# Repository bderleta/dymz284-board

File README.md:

# dymz284-board
Dual YMZ284 synth board design using retro technology (THT elements, DIP packages). Board designed to fit Hammond 1455C802 enclosure.

An application of ATMega8 8-bit MCU in PDIP package capable of driving two of YMZ284 PSG chips. This is a simplified derivative of [DYM2149](https://github.com/bderleta/dym2149-board) and runs similar firmware, but there are some differences:

- PSG data inputs are driven from '595 shift register controlled via SPI, instead of `PORTA` (note: '595 used has to be capable of running at 8 MHz+, as firmware uses SPI2X, making SPI clock equal to Tosc/2; plain SN74HC595 won't make it)
- Control pin assignments and names are different
- There is no JTAG and no SPI RAM
- Instead of single INT2 button, there are two hardware-debounced interrupt triggering buttons (INT0 and INT1)

As YMZ284 has only single DAC output, there is no mixing stage present, first PSG is assigned to the left channel, second - to the right. In contrary to YM2149 chips, YMZ has clock divider permamently enabled, therefore it is necessary to provide generator twice as fast to achieve identical behavior. This device has been tested with 4 MHz and 3.579545 MHz CXOs.

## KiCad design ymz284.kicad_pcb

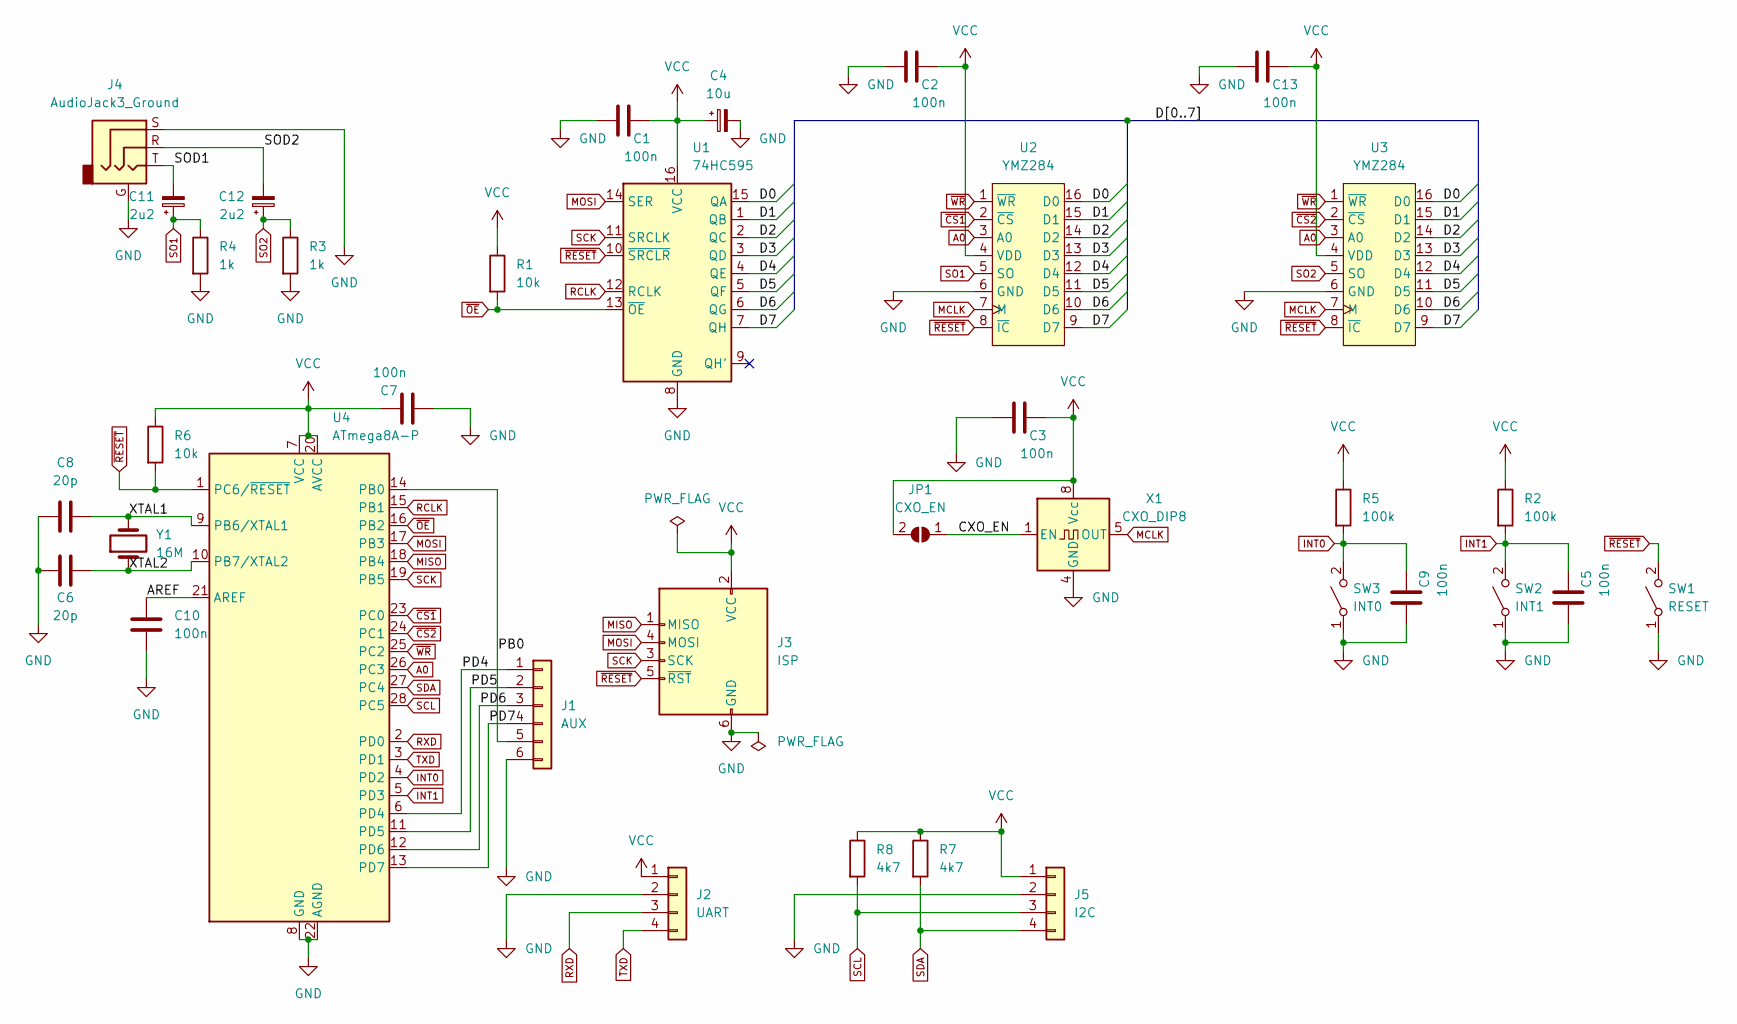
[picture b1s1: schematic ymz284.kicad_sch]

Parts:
C1, C2, C3, C5, C7, C9, C10, C13: 100n; C_Disc_D5.0mm_W2.5mm_P5.00mm
C4: 10u; CP_Radial_D5.0mm_P2.50mm
C6, C8: 20p; C_Disc_D5.0mm_W2.5mm_P5.00mm
C11, C12: 2u2; CP_Radial_D5.0mm_P2.50mm
J1: AUX; PinHeader_1x06_P2.54mm_Vertical
J2: UART; PinHeader_1x04_P2.54mm_Horizontal
J3: ISP; IDC-Header_2x03_P2.54mm_Vertical
J4: AudioJack3_Ground; Jack_6.35mm_Neutrik_NRJ3HF-1_Horizontal
J5: I2C; PinHeader_1x04_P2.54mm_Vertical
JP1: CXO_EN; SolderJumper-2_P1.3mm_Open_RoundedPad1.0x1.5mm
R1, R6: 10k; R_Axial_DIN0204_L3.6mm_D1.6mm_P5.08mm_Horizontal
R2, R5: 100k; R_Axial_DIN0204_L3.6mm_D1.6mm_P5.08mm_Horizontal
R3, R4: 1k; R_Axial_DIN0207_L6.3mm_D2.5mm_P7.62mm_Horizontal
R7, R8: 4k7; R_Axial_DIN0204_L3.6mm_D1.6mm_P5.08mm_Horizontal
SW1: RESET; SW_Tactile_SPST_Angled_PTS645Vx83-2LFS
SW2: INT1; SW_Tactile_SPST_Angled_PTS645Vx83-2LFS
SW3: INT0; SW_Tactile_SPST_Angled_PTS645Vx83-2LFS
U1: 74HC595; DIP-16_W7.62mm_Socket
U2, U3: YMZ284; DIP-16_W7.62mm_Socket
U4: ATmega8A-P; DIP-28_W7.62mm_Socket
X1: CXO_DIP8; Oscillator_DIP-8
Y1: 16M; Crystal_HC49-4H_Vertical

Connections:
/AREF: C10.2, U4.21 (AREF)
/CXO_EN: JP1.1 (A), X1.1 (EN)
/D0: U1.15 (QA), U2.16 (D0), U3.16 (D0)
/D1: U1.1 (QB), U2.15 (D1), U3.15 (D1)
/D2: U1.2 (QC), U2.14 (D2), U3.14 (D2)
/D3: U1.3 (QD), U2.13 (D3), U3.13 (D3)
/D4: U1.4 (QE), U2.12 (D4), U3.12 (D4)
/D5: U1.5 (QF), U2.11 (D5), U3.11 (D5)
/D6: U1.6 (QG), U2.10 (D6), U3.10 (D6)
/D7: U1.7 (QH), U2.9 (D7), U3.9 (D7)
/PB0: J1.5, U4.14 (PB0)
/PD4: J1.1, U4.6 (PD4)
/PD5: J1.2, U4.11 (PD5)
/PD6: J1.3, U4.12 (PD6)
/PD7: J1.4, U4.13 (PD7)
/SOD1: C11.2, J4.T
/SOD2: C12.2, J4.R
/XTAL1: C8.1, U4.9 (PB6/XTAL1), Y1.2
/XTAL2: C6.2, U4.10 (PB7/XTAL2), Y1.1
A0: U2.3 (A0), U3.3 (A0), U4.26 (PC3)
GND: C1.1, C2.1, C3.1, C4.2, C5.1, C6.1, C7.1, C8.2, C9.1, C10.1, C13.1, J1.6, J2.2, J3.6 (GND), J4.G, J4.S, J5.2, R3.2, R4.2, SW1.1 (A), SW2.1 (A), SW3.1 (A), U1.8 (GND), U2.6 (GND), U3.6 (GND), U4.8 (GND), U4.22 (AGND), X1.4 (GND)
INT0: C9.2, R5.2, SW3.2 (B), U4.4 (PD2)
INT1: C5.2, R2.2, SW2.2 (B), U4.5 (PD3)
MCLK: U2.7 (M), U3.7 (M), X1.5 (OUT)
MISO: J3.1 (MISO), U4.18 (PB4)
MOSI: J3.4 (MOSI), U1.14 (SER), U4.17 (PB3)
RCLK: U1.12 (RCLK), U4.15 (PB1)
RXD: J2.3, U4.2 (PD0)
SCK: J3.3 (SCK), U1.11 (SRCLK), U4.19 (PB5)
SCL: J5.3, R8.2, U4.28 (PC5)
SDA: J5.4, R7.2, U4.27 (PC4)
SO1: C11.1, R4.1, U2.5 (SO)
SO2: C12.1, R3.1, U3.5 (SO)
TXD: J2.4, U4.3 (PD1)
VCC: C1.2, C2.2, C3.2, C4.1, C7.2, C13.2, J2.1, J3.2 (VCC), J5.1, JP1.2 (B), R1.1, R2.1, R5.1, R6.1, R7.1, R8.1, U1.16 (VCC), U2.4 (VDD), U3.4 (VDD), U4.7 (VCC), U4.20 (AVCC), X1.8 (Vcc)
~CS1: U2.2 (~CS), U4.23 (PC0)
~CS2: U3.2 (~CS), U4.24 (PC1)
~OE: R1.2, U1.13 (~OE), U4.16 (PB2)
~RESET: J3.5 (~RST), R6.2, SW1.2 (B), U1.10 (~SRCLR), U2.8 (~IC), U3.8 (~IC), U4.1 (PC6/~RESET)
~WR: U2.1 (~WR), U3.1 (~WR), U4.25 (PC2)

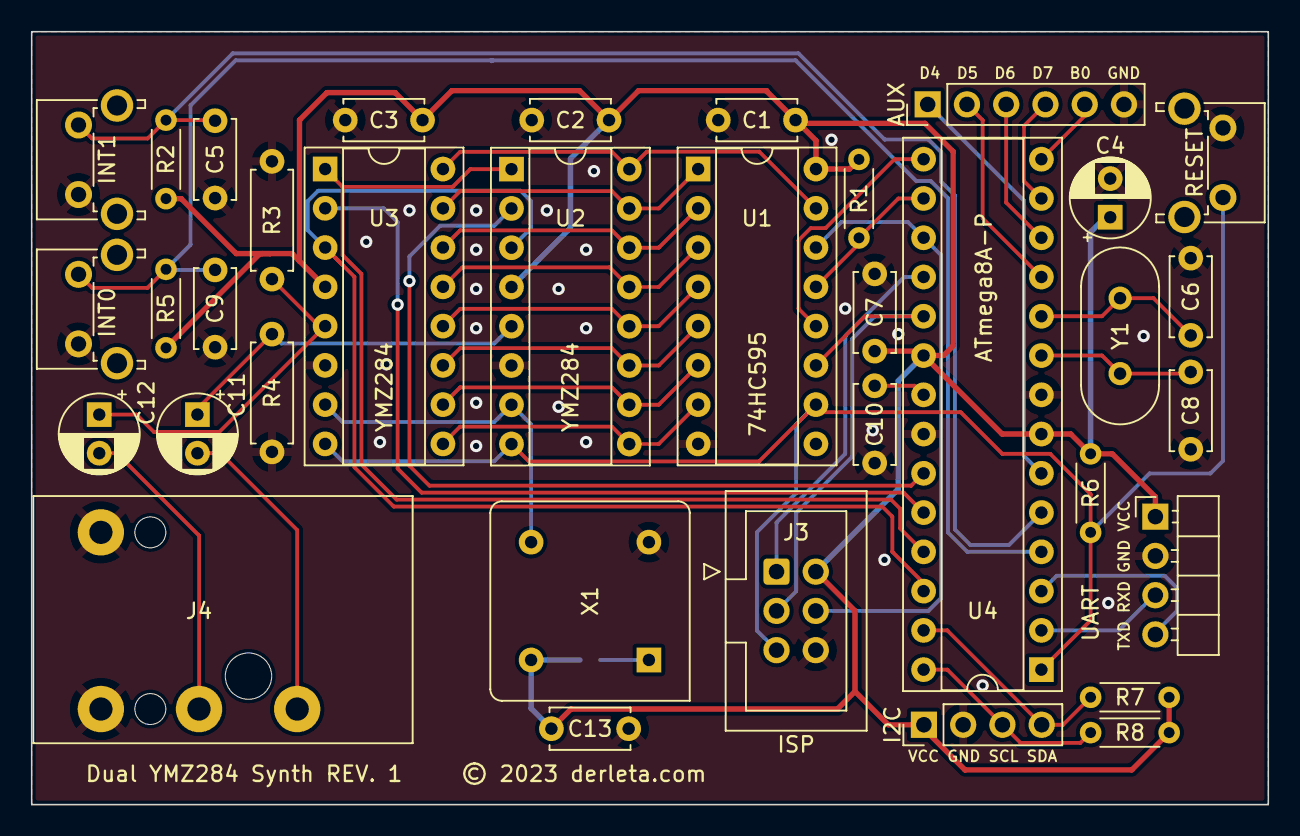
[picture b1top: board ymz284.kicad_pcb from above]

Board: 2 copper layers, 80.0 x 50.0 mm, 36 parts (1 on the bottom side), 40 nets.

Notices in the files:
ymz284.kicad_pcb:
Dual YMZ284 Synth REV. 1 © 2023 derleta.com
